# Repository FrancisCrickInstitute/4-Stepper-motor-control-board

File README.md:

# 4-Stepper-motor-control-board

Board to control 4 stepper motors based on the Teesny 3.5 dev. board. It has a small OLED display and 4 rotary encoders with switch and 2 DAC outputs in BNC connectors.

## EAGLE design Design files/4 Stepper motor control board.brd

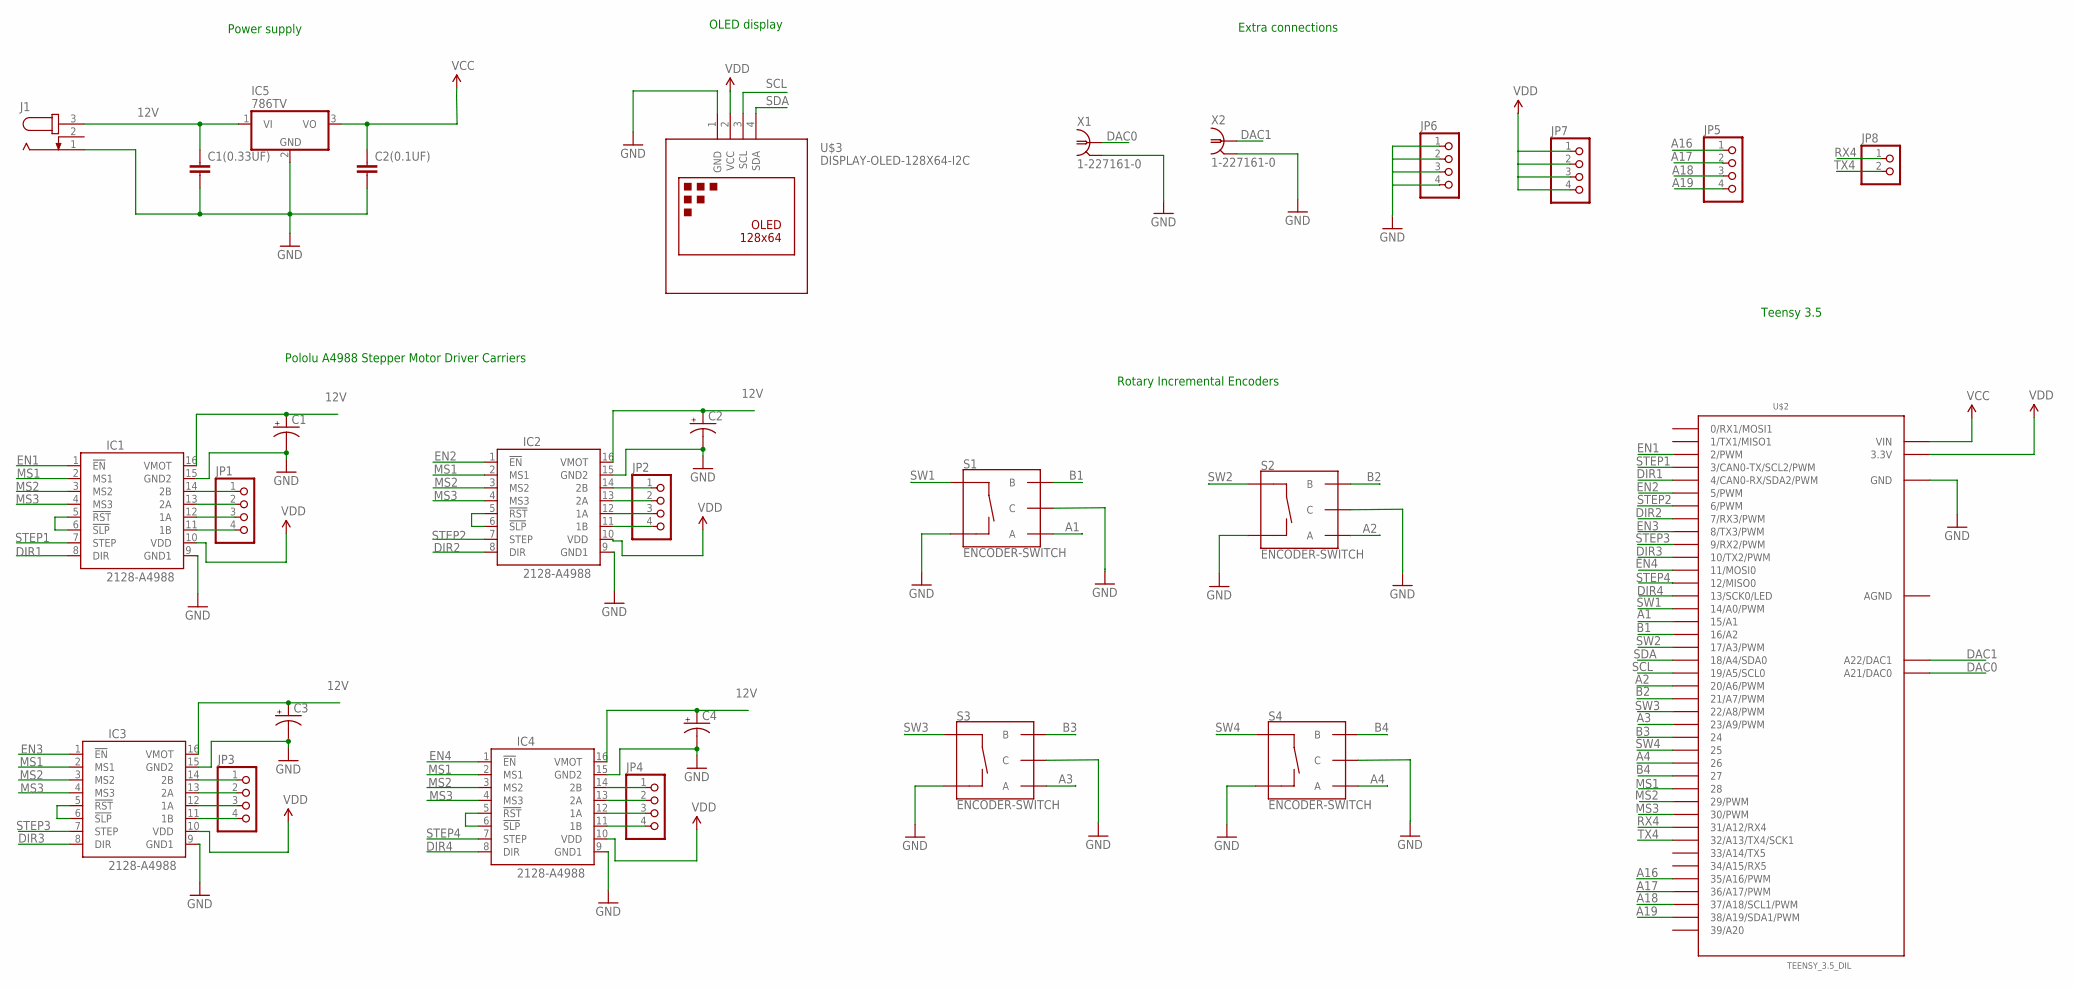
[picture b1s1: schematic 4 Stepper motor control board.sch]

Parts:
C1, C2, C3, C4: CPOL-USE5-5; E5-5
C1(0.33UF): C2.5/4; C2.5-4
C2(0.1UF): C2.5/2; C2.5-2
IC1, IC2, IC3, IC4: 2128-A4988; A4988
IC5: 786TV; TO220V
J1: JACK-PLUG0; SPC4077
JP1, JP2, JP3, JP4, JP5, JP6, JP7: PINHD-1X4; 1X04
JP8: PINHD-1X2; 1X02
S1, S2, S3, S4: ENCODER-SWITCH; ROTARY_ENC_PLAIN
U$2: TEENSY_3.5_DIL
U$3: DISPLAY-OLED-128X64-I2C
X1, X2: 1-227161-0; AMP_227161

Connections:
12V: C1.+, C1(0.33UF).1, C2.+, C3.+, C4.+, IC1.16 (VMOT), IC2.16 (VMOT), IC3.16 (VMOT), IC4.16 (VMOT), IC5.1 (VI), J1.3
A1: S1.A, U$2.15/A1
A2: S2.A, U$2.20/A6 (20/A6/PWM)
A3: S3.A, U$2.23/A9 (23/A9/PWM)
A4: S4.A, U$2.26
A16: JP5.1, U$2.35/A16 (35/A16/PWM)
A17: JP5.2, U$2.36/A17 (36/A17/PWM)
A18: JP5.3, U$2.37/A18 (37/A18/SCL1/PWM)
A19: JP5.4, U$2.38/A19 (38/A19/SDA1/PWM)
AGND: U$2.AGND
B1: S1.B, U$2.16/A2
B2: S2.B, U$2.21/A7 (21/A7/PWM)
B3: S3.B, U$2.24
B4: S4.B, U$2.27
DAC0: U$2.A21 (A21/DAC0), X1.1
DAC1: U$2.A22 (A22/DAC1), X2.1
DIR1: IC1.8 (DIR), U$2.4 (4/CAN0-RX/SDA2/PWM)
DIR2: IC2.8 (DIR), U$2.7 (7/RX3/PWM)
DIR3: IC3.8 (DIR), U$2.10 (10/TX2/PWM)
DIR4: IC4.8 (DIR), U$2.13 (13/SCK0/LED)
EN1: IC1.1 (!EN), U$2.2 (2/PWM)
EN2: IC2.1 (!EN), U$2.5 (5/PWM)
EN3: IC3.1 (!EN), U$2.8 (8/TX3/PWM)
EN4: IC4.1 (!EN), U$2.11 (11/MOSI0)
GND: C1.-, C1(0.33UF).2, C2.-, C2(0.1UF).2, C3.-, C4.-, IC1.9 (GND1), IC1.15 (GND2), IC2.9 (GND1), IC2.15 (GND2), IC3.9 (GND1), IC3.15 (GND2), IC4.9 (GND1), IC4.15 (GND2), IC5.2 (GND), J1.1, JP6.1, JP6.2, JP6.3, JP6.4, S1.C, S1.SW-, S2.C, S2.SW-, S3.C, S3.SW-, S4.C, S4.SW-, U$2.GND, U$2.GND1 (GND), U$3.1 (GND), X1.2, X2.2
MS1: IC1.2 (MS1), IC2.2 (MS1), IC3.2 (MS1), IC4.2 (MS1), U$2.28
MS2: IC1.3 (MS2), IC2.3 (MS2), IC3.3 (MS2), IC4.3 (MS2), U$2.29 (29/PWM)
MS3: IC1.4 (MS3), IC2.4 (MS3), IC3.4 (MS3), IC4.4 (MS3), U$2.30 (30/PWM)
unnamed: IC1.14 (2B), JP1.1
unnamed: IC1.13 (2A), JP1.2
unnamed: IC1.12 (1A), JP1.3
unnamed: IC1.11 (1B), JP1.4
unnamed: IC2.14 (2B), JP2.1
unnamed: IC2.13 (2A), JP2.2
unnamed: IC2.12 (1A), JP2.3
unnamed: IC2.11 (1B), JP2.4
unnamed: IC2.5 (!RST), IC2.6 (!SLP)
unnamed: IC1.5 (!RST), IC1.6 (!SLP)
unnamed: IC3.14 (2B), JP3.1
unnamed: IC3.13 (2A), JP3.2
unnamed: IC3.12 (1A), JP3.3
unnamed: IC3.11 (1B), JP3.4
unnamed: IC3.5 (!RST), IC3.6 (!SLP)
unnamed: IC4.14 (2B), JP4.1
unnamed: IC4.13 (2A), JP4.2
unnamed: IC4.12 (1A), JP4.3
unnamed: IC4.11 (1B), JP4.4
unnamed: IC4.5 (!RST), IC4.6 (!SLP)
RX4: JP8.1, U$2.31/A12 (31/A12/RX4)
SCL: U$2.19/A5 (19/A5/SCL0), U$3.3 (SCL)
SDA: U$2.18/A4 (18/A4/SDA0), U$3.4 (SDA)
STEP1: IC1.7 (STEP), U$2.3 (3/CAN0-TX/SCL2/PWM)
STEP2: IC2.7 (STEP), U$2.6 (6/PWM)
STEP3: IC3.7 (STEP), U$2.9 (9/RX2/PWM)
STEP4: IC4.7 (STEP), U$2.12 (12/MISO0)
SW1: S1.SW+, U$2.14/A0 (14/A0/PWM)
SW2: S2.SW+, U$2.17/A3 (17/A3/PWM)
SW3: S3.SW+, U$2.22/A8 (22/A8/PWM)
SW4: S4.SW+, U$2.25
TX4: JP8.2, U$2.32/A13 (32/A13/TX4/SCK1)
VCC: C2(0.1UF).1, IC5.3 (VO), U$2.VIN
VDD: IC1.10 (VDD), IC2.10 (VDD), IC3.10 (VDD), IC4.10 (VDD), JP7.1, JP7.2, JP7.3, JP7.4, U$2.3.3V, U$2.3.3V3 (3.3V), U$3.2 (VCC)

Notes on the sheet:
Pololu A4988 Stepper Motor Driver Carriers
OLED display
Power supply
Rotary Incremental Encoders
Teensy 3.5
Extra connections

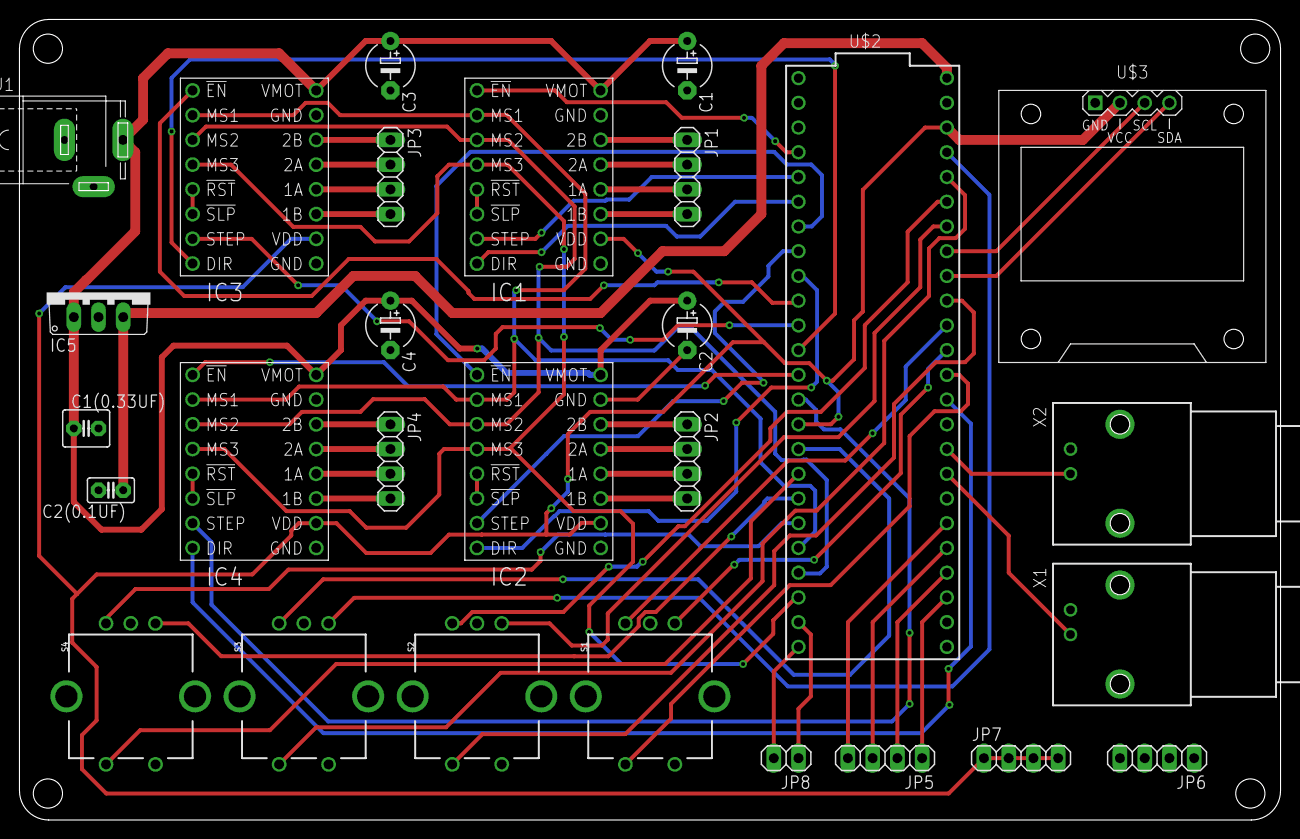
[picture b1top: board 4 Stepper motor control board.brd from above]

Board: 2 copper layers, 129.5 x 82.2 mm, 28 parts (0 on the bottom side), 61 nets.

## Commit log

2021-07-29 Second commit
2021-08-13 Example code1

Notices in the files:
parts and their libraries:
diy-modules: Released under the Creative Commons Attribution 4.0 International License: http://creativecommons.org/licenses/by/4.0
SparkFun-Switches: Licensing: Creative Commons ShareAlike 4.0 International - https://creativecommons.org/licenses/by-sa/4.0
